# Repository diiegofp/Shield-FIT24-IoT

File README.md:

# Shield FIT24-IoT
Este dispositivo fue creado para el track de IoT en el Foro de Innovación Tecnológica (FIT), evento organizado en Universidad Galileo por el laboratorio de Investigación Tesla Lab. Además, fue diseñado y ensamblado en Guatemala. Su principal objetivo es mandar datos del sensor BME680 a través de la tecnología LoRa.

# ¿Qué podemos hacer?

Desplegar información por medio de un web server o dashboard a través de LoRa. Obtener mediciones de temperatura, humedad y presión atmosférica a través del sensor BME680. Además, cuenta con 3 Neopixeles, un Buzzer para emitir algún sonido o alerta y pin headers para conectar otro dispositivo por I2C.

# Pinout

### Buzzer
Nombre | PIN 
--- | --- 
IN | 10
VDD | 5V
VSS | GND

### NPX - WS2812B
Nombre | PIN 
--- | --- 
DIN | 11
VDD | 5V
VSS | GND

### Sensor de temperatura, humedad, presión y gas  - Comunicación I2C 
BME680 | RAK4260
--- | ---
SDI 3 | SDA PA16
SCK 4 |  SCL PA17

# Licencia

Hardware License: CERN Open Hardware License Version 2.0

Software License: GNU General Public License Version 3.0

Documentation License: CC BY 4.0 International

# Contacto

Autor: Diego Iboy (diego.iboy@galileo.edu)

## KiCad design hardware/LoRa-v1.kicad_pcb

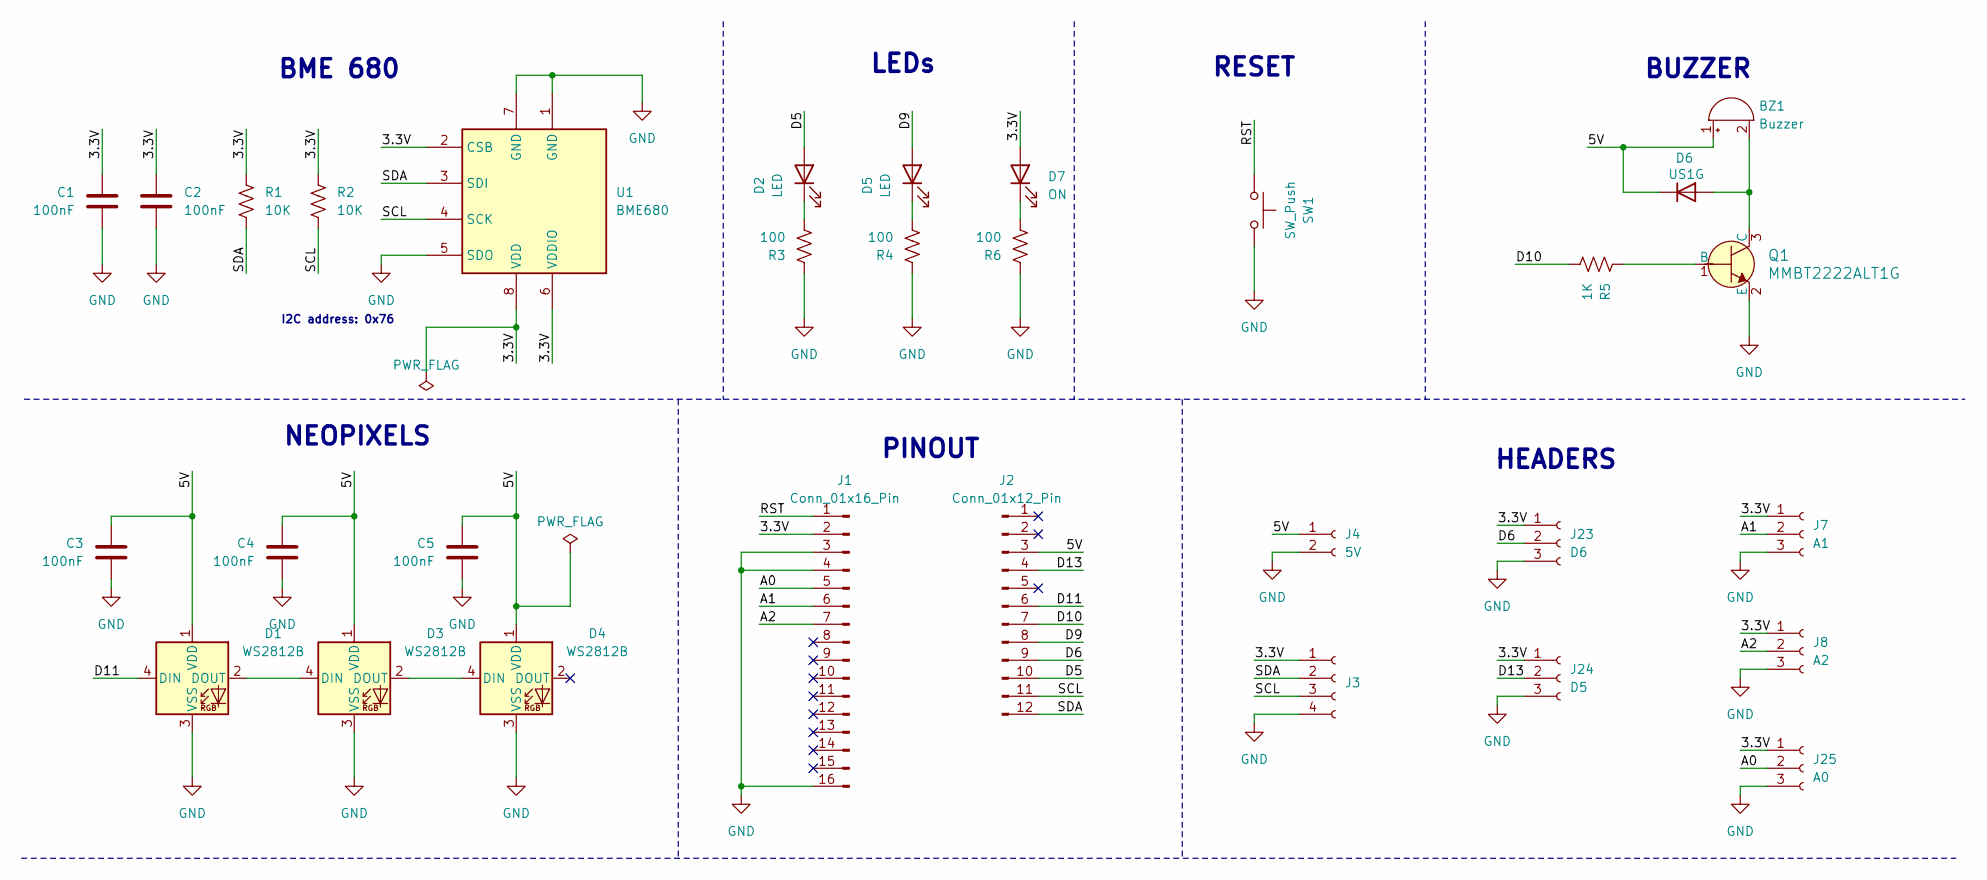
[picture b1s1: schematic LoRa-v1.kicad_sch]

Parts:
BZ1: Buzzer; Buzzer_TDK_PS1240P02BT_D12.2mm_H6.5mm
C1, C2, C3, C4, C5: 100nF; C_0805_2012Metric
D1, D3, D4: WS2812B; LED_WS2812B_PLCC4_5.0x5.0mm_P3.2mm
D2, D5: LED; LED_1206_3216Metric
D6: US1G; D_SMA
D7: ON; LED_1206_3216Metric
J1: Conn_01x16_Pin; PinSocket_1x16_P2.54mm_Vertical
J2: Conn_01x12_Pin; PinSocket_1x12_P2.54mm_Vertical
J3: PinHeader_1x04_P2.54mm_Vertical
J4: 5V; PinHeader_1x02_P2.54mm_Vertical
J7: A1; PinHeader_1x03_P2.54mm_Vertical
J8: A2; PinHeader_1x03_P2.54mm_Vertical
J23: D6; PinHeader_1x03_P2.54mm_Vertical
J24: D5; PinHeader_1x03_P2.54mm_Vertical
J25: A0; PinHeader_1x03_P2.54mm_Vertical
Q1: MMBT2222ALT1G; SOT-23-3; MPN MMBT2222ALT1G; Digi-Key_PN MMBT2222ALT1GOSCT-ND
R1, R2: 10K; R_0805_2012Metric
R3, R4, R6: 100; R_0805_2012Metric
R5: 1K; R_0805_2012Metric
SW1: SW_Push; SW_SPST_B3U-3100P-B
U1: BME680; Bosch_LGA-8_3x3mm_P0.8mm_ClockwisePinNumbering

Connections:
/3.3V: C1.1, C2.1, D7.2 (A), J1.2, J3.1, J7.1, J8.1, J23.1, J24.1, J25.1, R1.1, R2.1, U1.2 (CSB), U1.6 (VDDIO), U1.8 (VDD)
/5V: BZ1.1 (+), C3.1, C4.1, C5.1, D1.1 (VDD), D3.1 (VDD), D4.1 (VDD), D6.1 (K), J2.3, J4.1
/A0: J1.5, J25.2
/A1: J1.6, J7.2
/A2: J1.7, J8.2
/D5: D2.2 (A), J2.10
/D6: J2.9, J23.2
/D9: D5.2 (A), J2.8
/D10: J2.7, R5.1
/D11: D1.4 (DIN), J2.6
/D13: J2.4, J24.2
/RST: J1.1, SW1.2
/SCL: J2.11, J3.3, R2.2, U1.4 (SCK)
/SDA: J2.12, J3.2, R1.2, U1.3 (SDI)
GND: C1.2, C2.2, C3.2, C4.2, C5.2, D1.3 (VSS), D3.3 (VSS), D4.3 (VSS), J1.3, J1.4, J1.16, J3.4, J4.2, J7.3, J8.3, J23.3, J24.3, J25.3, Q1.2 (E), R3.2, R4.2, R6.2, SW1.1, U1.1 (GND), U1.5 (SDO), U1.7 (GND)
unnamed: BZ1.2 (-), D6.2 (A), Q1.3 (C)
unnamed: D1.2 (DOUT), D3.4 (DIN)
unnamed: D2.1 (K), R3.1
unnamed: D3.2 (DOUT), D4.4 (DIN)
unnamed: D5.1 (K), R4.1
unnamed: D7.1 (K), R6.1
unnamed: Q1.1 (B), R5.2

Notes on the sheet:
I2C address: 0x76
NEOPIXELS
HEADERS
RESET
PINOUT
BME 680
LEDs
BUZZER

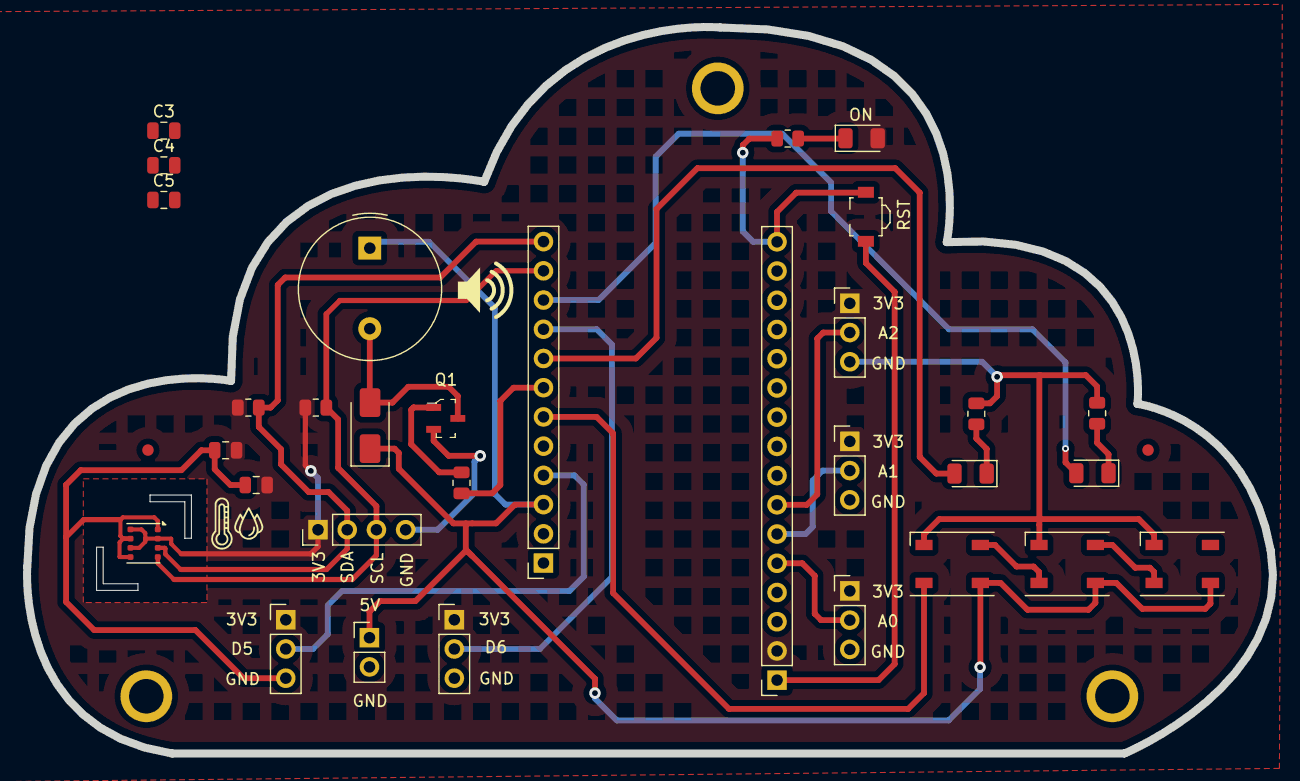
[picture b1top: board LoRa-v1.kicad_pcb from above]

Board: 2 copper layers, 108.3 x 63.1 mm, 31 parts (0 on the bottom side), 22 nets.

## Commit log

2025-04-05 Create Hardware
